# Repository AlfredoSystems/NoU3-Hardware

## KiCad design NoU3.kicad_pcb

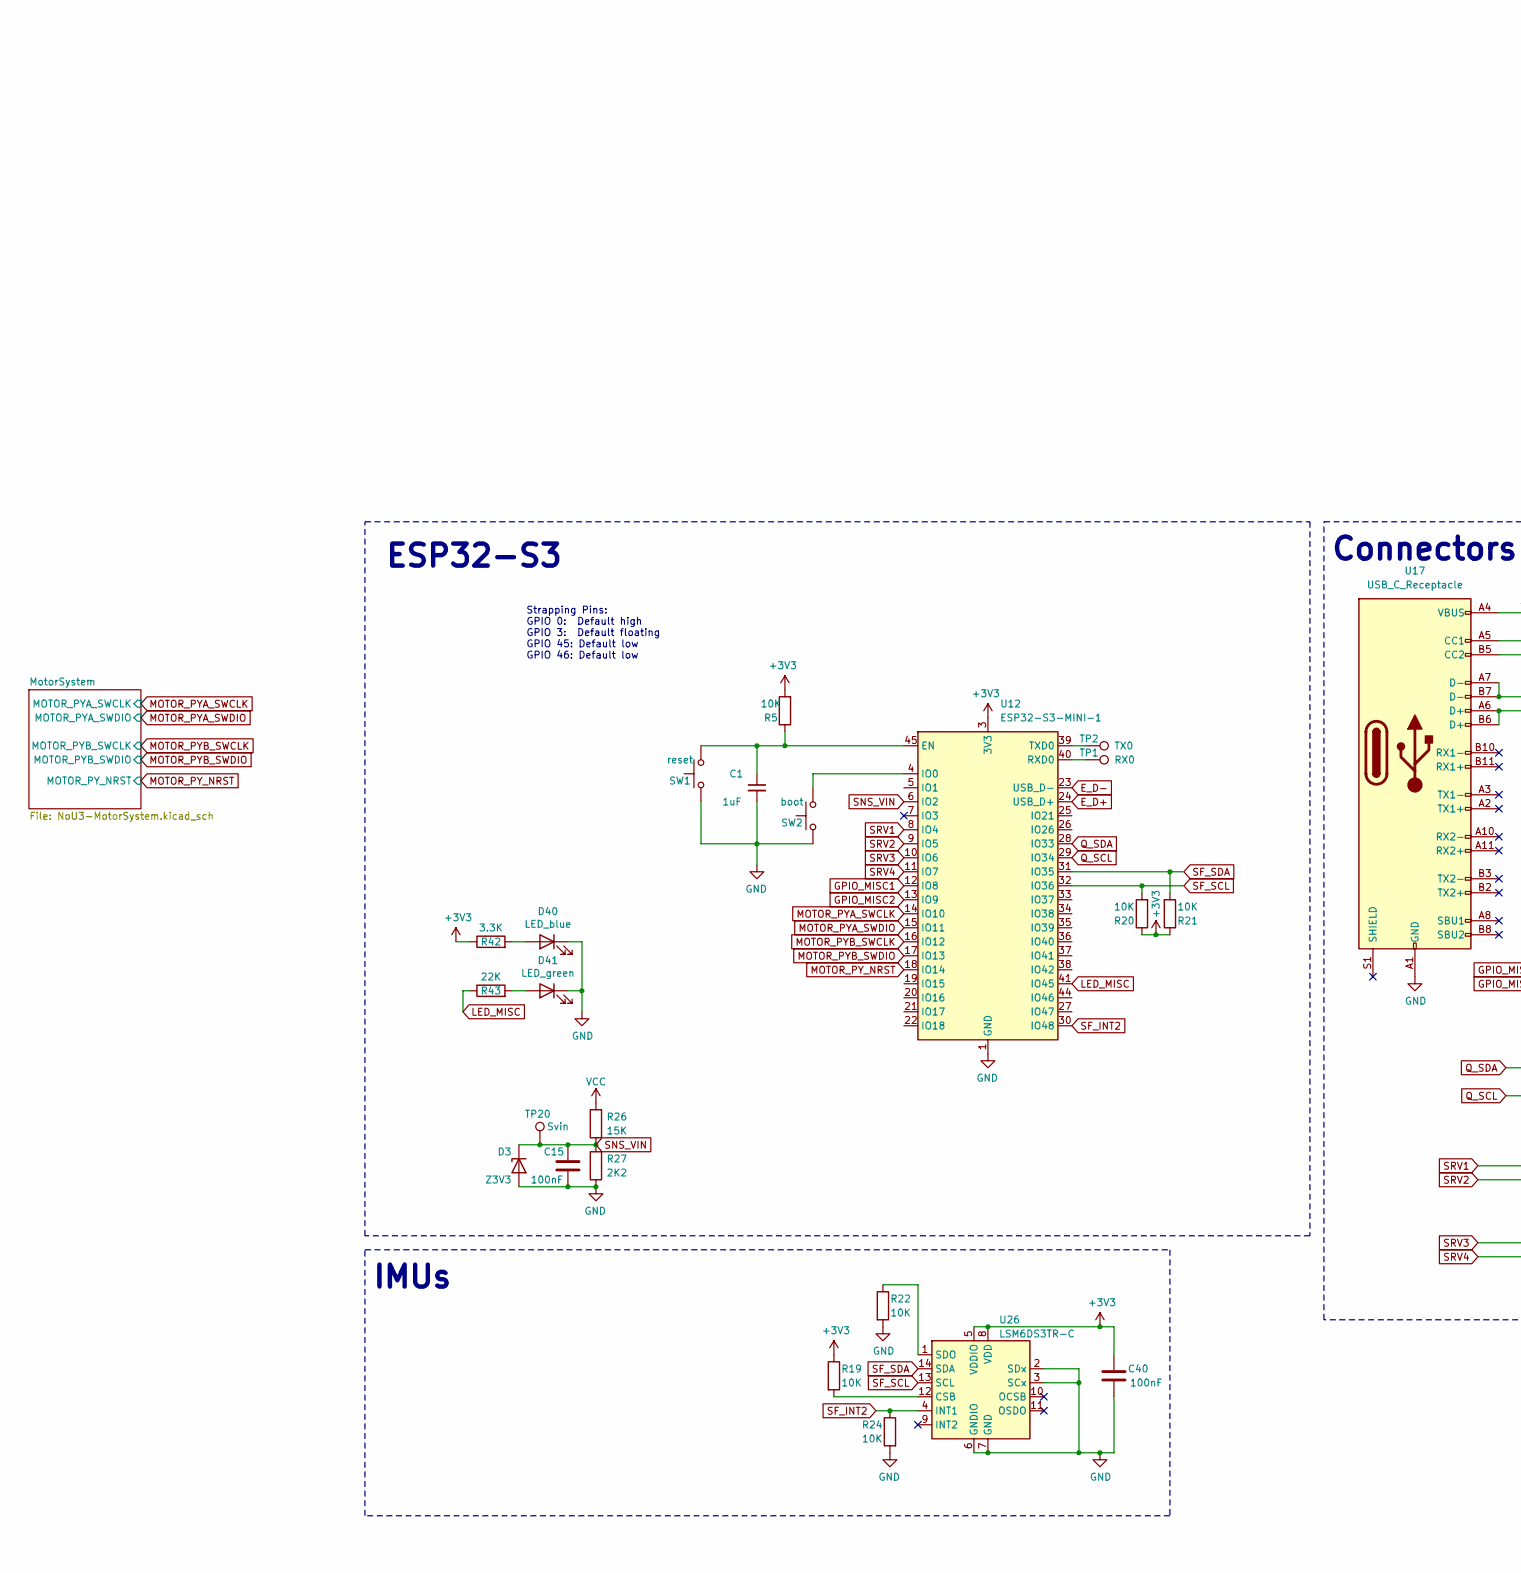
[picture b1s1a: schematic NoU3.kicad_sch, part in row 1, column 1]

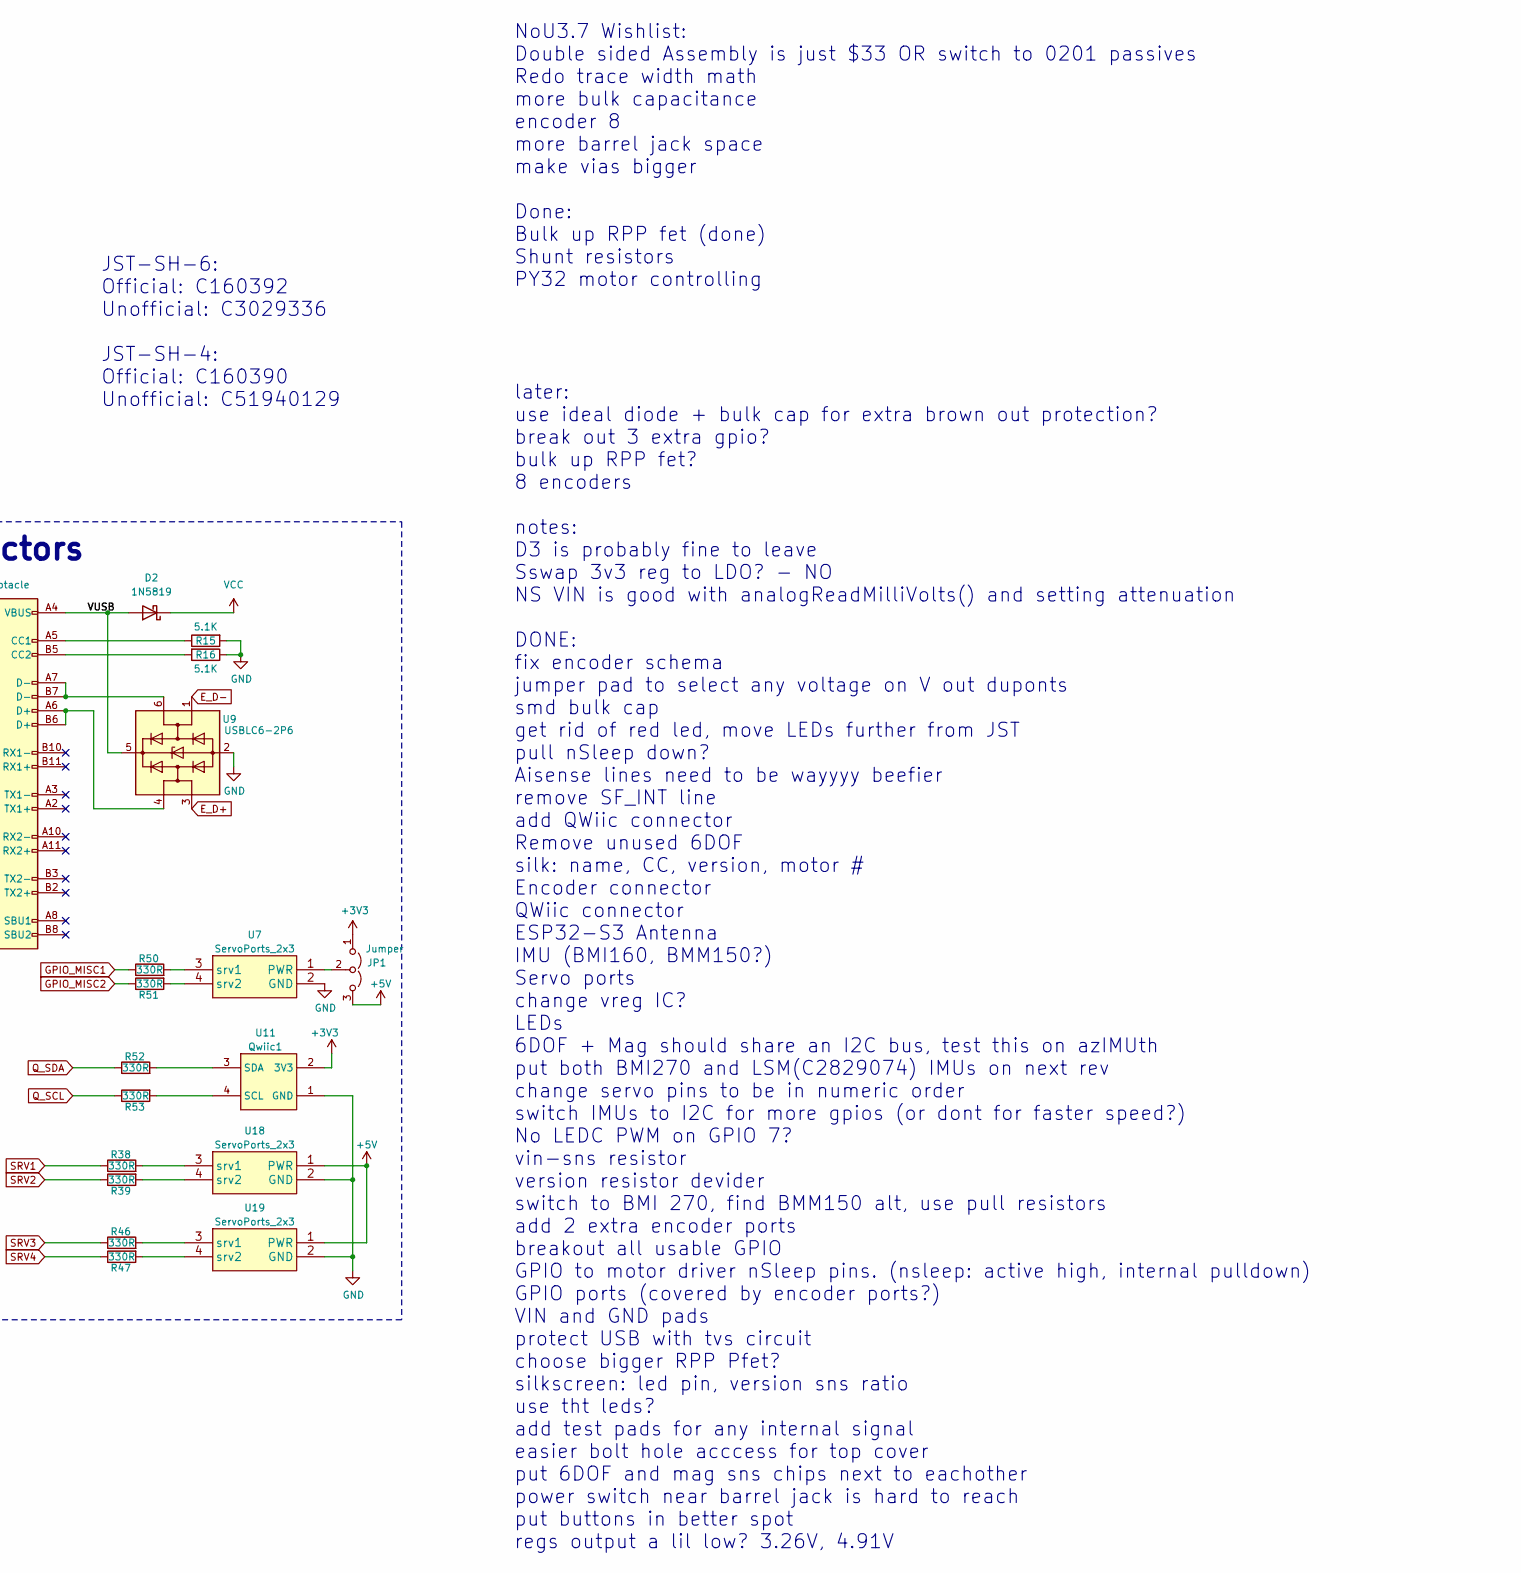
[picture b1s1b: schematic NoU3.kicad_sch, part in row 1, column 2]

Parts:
C1: 1uF; C_0402_1005Metric; LCSC C52923
C15, C40: 100nF; C_0402_1005Metric; LCSC C307331
D2: 1N5819; D_SOD-323; LCSC C191023
D3: Z3V3; D_SOD-323; LCSC C75073
D40: LED_blue; LED_0402_1005Metric; LCSC C130724
D41: LED_green; LED_0402_1005Metric; LCSC C965793
JP1: Jumper; SolderJumper-3-Small
R5, R19, R20, R21, R22, R24: 10K; R_0402_1005Metric; LCSC C25744
R15, R16: 5.1K; R_0402_1005Metric; LCSC C25905
R26: 15K; R_0402_1005Metric; LCSC C25756
R27: 2K2; R_0402_1005Metric; LCSC C25879
R38, R39, R46, R47, R50, R51, R52, R53: 330R; R_0402_1005Metric; LCSC C25104
R42: 3.3K; R_0402_1005Metric; LCSC C25890
R43: 22K; R_0402_1005Metric; LCSC C25768
SW1: reset; Button_SKRKAEE020; LCSC C115357
SW2: boot; Button_SKRKAEE020; LCSC C115357
TP1: RX0; PogoPad1
TP2: TX0; PogoPad1
TP20: Svin; PogoPad1
U7, U18, U19: ServoPorts_2x3; LCSC C5116479
U9: USBLC6-2P6; SOT-666; LCSC C2827693
U11: Qwiic1; JST_SH_BM04B-SRSS-TB_1x04-1MP_P1.00mm_Vertical; LCSC C51940129
U12: ESP32-S3-MINI-1; ESP32-S2-MINI-1; LCSC C2913206
U17: USB_C_Receptacle; USB_TYPE-C-31-M-12; LCSC C165948
U26: LSM6DS3TR-C; Bosch_LGA-14_3x2.5mm_P0.5mm; LCSC C967633

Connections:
+3V3: C40.1, JP1.1 (A), R5.2, R19.1, R20.1, R21.1, R42.1, U11.2 (3V3), U12.3 (3V3), U26.5 (VDDIO), U26.8 (VDD); also elsewhere on the board
+5V: JP1.3 (B), U18.1 (PWR), U19.1 (PWR); also elsewhere on the board
/VUSB: D2.2 (A), U9.5 (VBUS), U17.A4 (VBUS), U17.A9 (VBUS), U17.B4 (VBUS), U17.B9 (VBUS)
E_D+: U9.3 (I/O2), U12.24 (USB_D+)
E_D-: U9.1 (I/O1), U12.23 (USB_D-)
GND: C1.2, C15.2, C40.2, D3.2 (A), D40.1 (K), D41.1 (K), R15.2, R16.1, R22.2, R24.2, R27.1, SW1.2, SW2.2, U7.2 (GND), U9.2 (GND), U11.1 (GND), U12.1 (GND), U12.2 (GND), U12.42 (GND), U12.43 (GND), U12.46 (GND), U12.47 (GND), U12.48 (GND), U12.49 (GND), U12.50 (GND), U12.51 (GND), U12.52 (GND), U12.53 (GND), U12.54 (GND), U12.55 (GND), U12.56 (GND), U12.57 (GND), U12.58 (GND), U12.59 (GND), U12.60 (GND), U12.61 (GND), U12.62 (GND), U12.63 (GND), U12.64 (GND), U12.65 (GND), U17.A1 (GND), U17.A12 (GND), U17.B1 (GND), U17.B12 (GND), U18.2 (GND), U19.2 (GND), U26.2 (SDx), U26.3 (SCx), U26.6 (GNDIO), U26.7 (GND); also elsewhere on the board
GPIO_MISC1: R50.1, U12.12 (IO8)
GPIO_MISC2: R51.1, U12.13 (IO9)
LED_MISC: R43.1, U12.41 (IO45)
MOTOR_PYA_SWCLK: U12.14 (IO10); also elsewhere on the board
MOTOR_PYA_SWDIO: U12.15 (IO11); also elsewhere on the board
MOTOR_PYB_SWCLK: U12.16 (IO12); also elsewhere on the board
MOTOR_PYB_SWDIO: U12.17 (IO13); also elsewhere on the board
MOTOR_PY_NRST: U12.18 (IO14); also elsewhere on the board
unnamed: D40.2 (A), R42.2
unnamed: D41.2 (A), R43.2
unnamed: JP1.2 (C), U7.1 (PWR)
unnamed: R50.2, U7.3 (srv1)
unnamed: R51.2, U7.4 (srv2)
unnamed: R53.2, U11.4 (SCL)
unnamed: R52.2, U11.3 (SDA)
unnamed: C1.1, R5.1, SW1.1, U12.45 (EN)
unnamed: SW2.1, U12.4 (IO0)
unnamed: TP1.1 (1_1), U12.40 (RXD0)
unnamed: TP2.1 (1_1), U12.39 (TXD0)
unnamed: R15.1, U17.A5 (CC1)
unnamed: R16.2, U17.B5 (CC2)
unnamed: U9.4 (I/O2), U17.A6 (D+), U17.B6 (D+)
unnamed: U9.6 (I/O1), U17.A7 (D-), U17.B7 (D-)
unnamed: R38.2, U18.3 (srv1)
unnamed: R39.2, U18.4 (srv2)
unnamed: R46.2, U19.3 (srv1)
unnamed: R47.2, U19.4 (srv2)
unnamed: R19.2, U26.12 (CSB)
unnamed: R22.1, U26.1 (SDO)
Q_SCL: R53.1, U12.29 (IO34)
Q_SDA: R52.1, U12.28 (IO33)
SF_INT2: R24.1, U12.30 (IO48), U26.4 (INT1)
SF_SCL: R20.2, U12.32 (IO36), U26.13 (SCL)
SF_SDA: R21.2, U12.31 (IO35), U26.14 (SDA)
SNS_VIN: C15.1, D3.1 (K), R26.1, R27.2, TP20.1 (1_1), U12.6 (IO2)
SRV1: R38.1, U12.8 (IO4)
SRV2: R39.1, U12.9 (IO5)
SRV3: R46.1, U12.10 (IO6)
SRV4: R47.1, U12.11 (IO7)
VCC: D2.1 (K), R26.2; also elsewhere on the board

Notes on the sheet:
IMUs
Strapping Pins: GPIO 0: Default high GPIO 3: Default floating GPIO 45: Default low GPIO 46: Default low
NoU3.7 Wishlist: Double sided Assembly is just $33 OR switch to 0201 passives Redo trace width math more bulk capacitance encoder 8 more barrel jack space make vias bigger Done: Bulk up RPP fet (done) Shunt resistors PY32 motor controlling later: use ideal diode + bulk cap for extra brown out prote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
Connectors
ESP32-S3
JST-SH-6: Official: C160392 Unofficial: C3029336 JST-SH-4: Official: C160390 Unofficial: C51940129

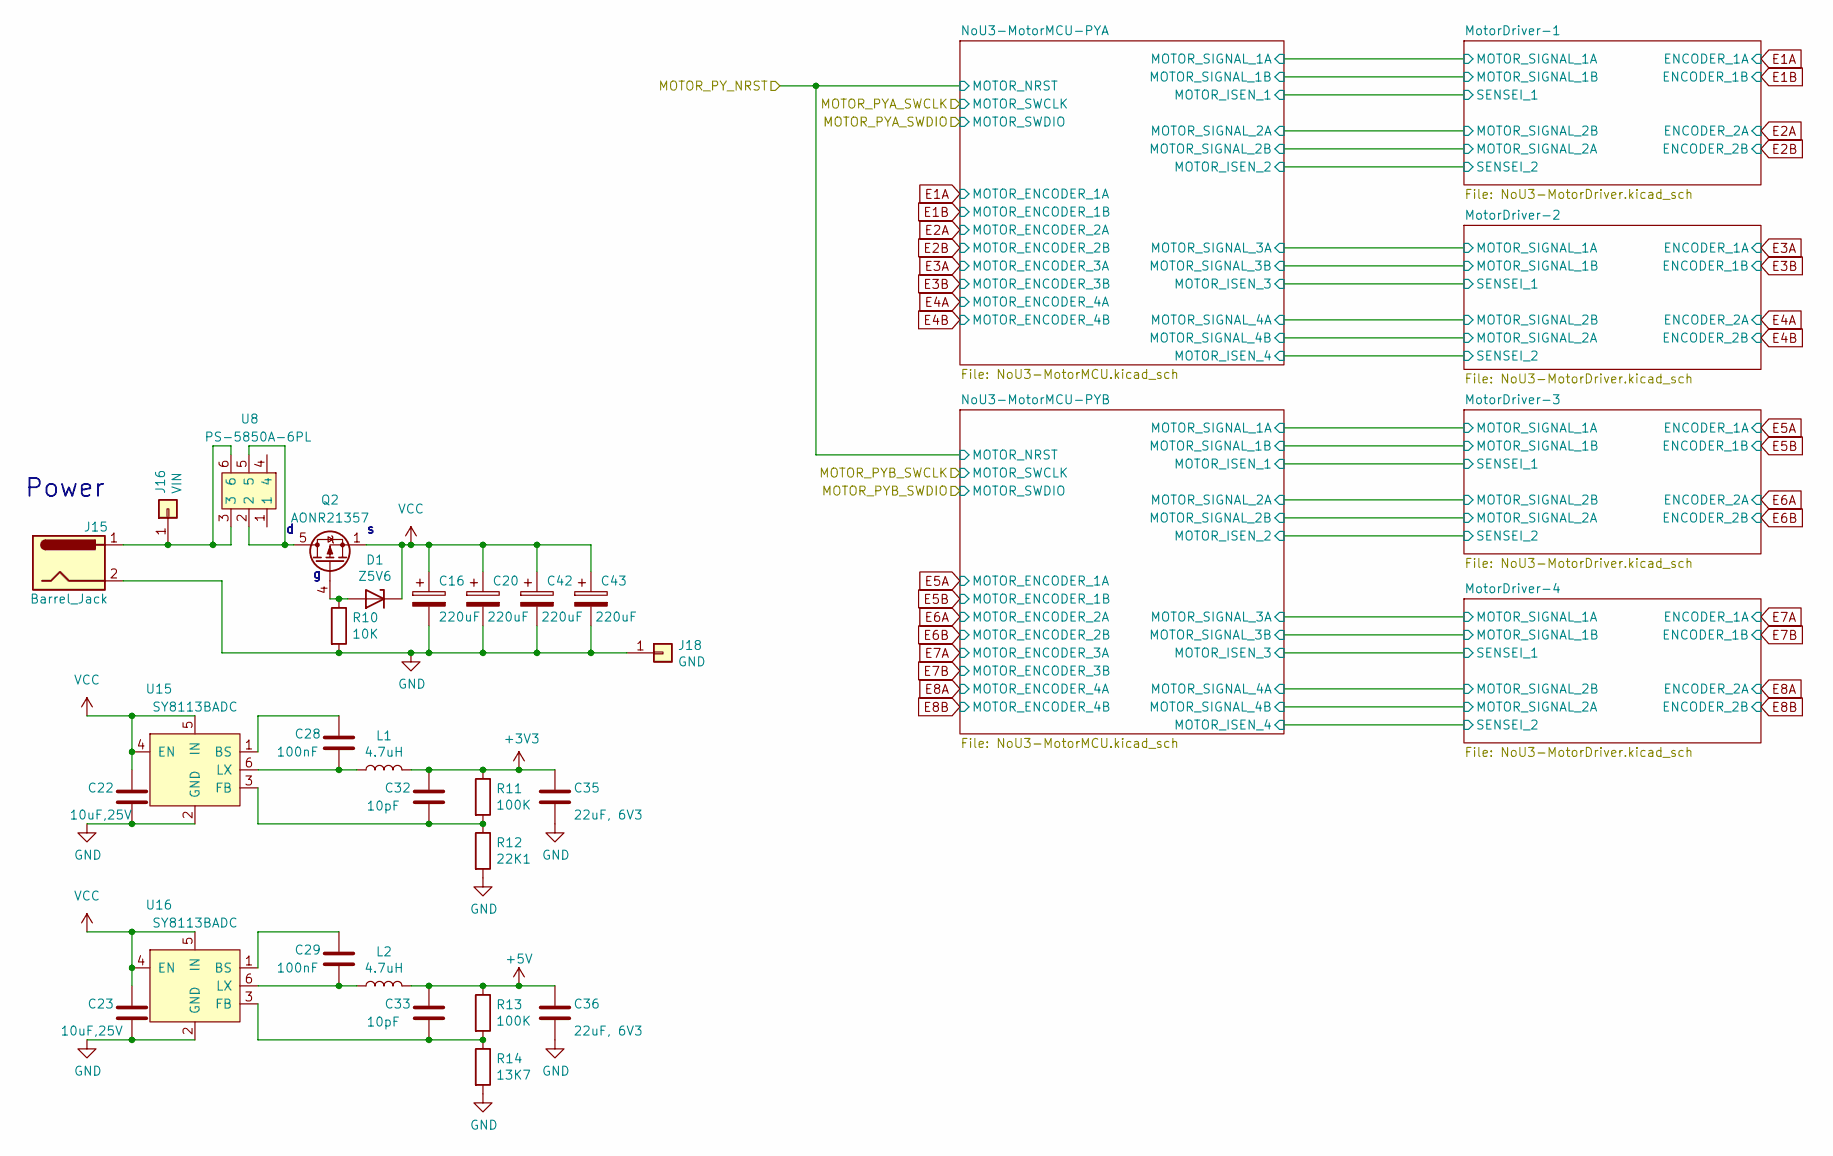
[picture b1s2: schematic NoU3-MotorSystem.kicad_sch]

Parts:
C16, C20, C42, C43: 220uF; CP_Elec_6.3x7.7_slim; LCSC C4747974
C22, C23: 10uF,25V; C_0603_1608Metric; LCSC C96446
C28, C29: 100nF; C_0402_1005Metric; LCSC C307331
C32, C33: 10pF; C_0402_1005Metric; LCSC C32949
C35, C36: 22uF, 6V3; C_0603_1608Metric; LCSC C59461
D1: Z5V6; D_SOD-323; LCSC C22612
J15: Barrel_Jack; DC-005C_1; LCSC C84007
J16: VIN; PinSocket_1x01_P2.54mm_Vertical
J18: GND; PinSocket_1x01_P2.54mm_Vertical
L1, L2: 4.7uH; LVF252A12; LCSC C88528
Q2: AONR21357; DFN-8-1EP_3x3mm_P0.65mm_EP1.55x2.4mm; LCSC C431196
R10: 10K; R_0402_1005Metric; LCSC C25744
R11, R13: 100K; R_0402_1005Metric; LCSC C25741
R12: 22K1; R_0402_1005Metric; LCSC C163478
R14: 13K7; R_0402_1005Metric; LCSC C25854
U8: PS-5850A-6PL; XKB5858-Z-75; LCSC C963201
U15, U16: SY8113BADC; TSOT-23-6; LCSC C78989

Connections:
+3V3: C32.1, C35.1, L1.2, R11.1; also elsewhere on the board
+5V: C33.1, C36.1, L2.2, R13.1; also elsewhere on the board
GND: C16.2, C20.2, C22.2, C23.2, C35.2, C36.2, C42.2, C43.2, J15.2, J18.1 (Pin_1_1), R10.2, R12.2, R14.2, U15.2 (GND), U16.2 (GND); also elsewhere on the board
unnamed: D1.2 (A), Q2.4 (G), R10.1
unnamed: J15.1, J16.1 (Pin_1_1), U8.3, U8.6
unnamed: Q2.5 (D), Q2.6 (D), Q2.7 (D), Q2.8 (D), Q2.9 (D), U8.2, U8.5
unnamed: C28.1, U15.1 (BS)
unnamed: C32.2, R11.2, R12.1, U15.3 (FB)
unnamed: C28.2, L1.1, U15.6 (LX)
unnamed: C29.1, U16.1 (BS)
unnamed: C33.2, R13.2, R14.1, U16.3 (FB)
unnamed: C29.2, L2.1, U16.6 (LX)
VCC: C16.1, C20.1, C22.1, C23.1, C42.1, C43.1, D1.1 (K), Q2.1 (S), Q2.2 (S), Q2.3 (S), U15.4 (EN), U15.5 (IN), U16.4 (EN), U16.5 (IN); also elsewhere on the board

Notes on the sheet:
Power

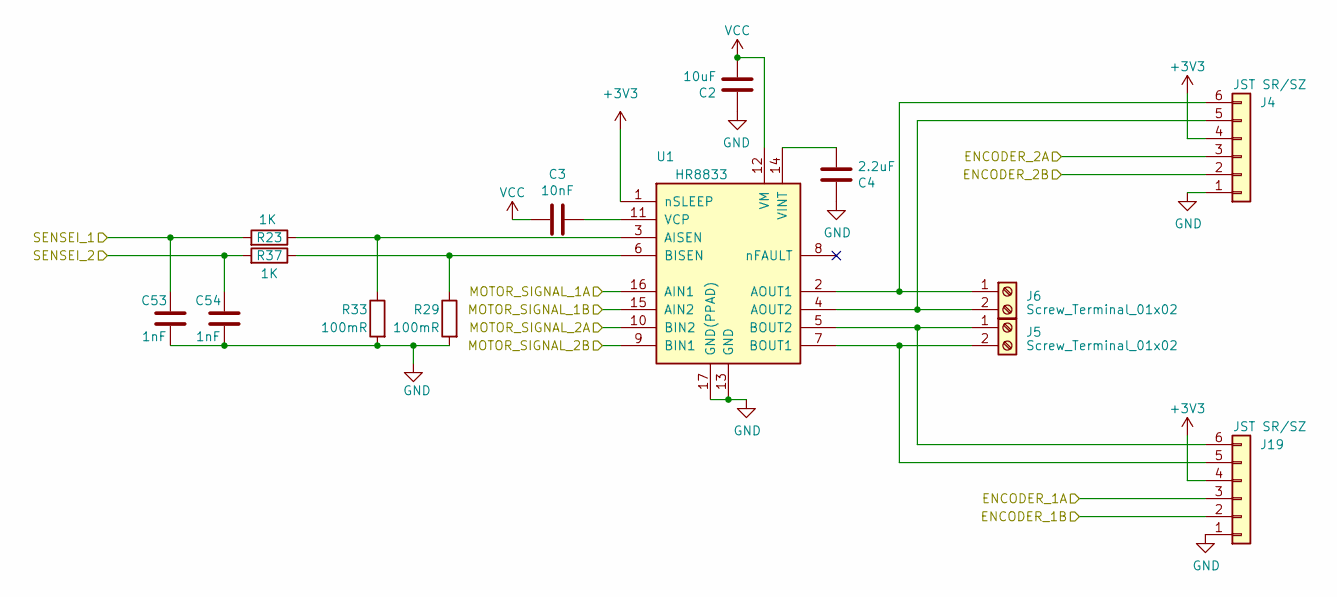
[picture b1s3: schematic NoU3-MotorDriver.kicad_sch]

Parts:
C2: 10uF; C_0805_2012Metric; LCSC C15850
C3: 10nF; C_0402_1005Metric; LCSC C15195
C4: 2.2uF; C_0402_1005Metric; LCSC C12530
C53, C54: 1nF; C_0402_1005Metric; LCSC C1523
J4, J19: JST SR/SZ; JST_SH_1x06_Vertical; LCSC C3029336
J5, J6: Screw_Terminal_01x02; TerminalBlock_Ningbo_2P_5mm; LCSC C557646
R23, R37: 1K; R_0402_1005Metric; LCSC C11702
R29, R33: 100mR; R_0805_2012Metric; LCSC C327057
U1: HR8833; HR8833-0.6mm; LCSC C128666

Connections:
+3V3: J4.4, J19.4, U1.1 (nSLEEP); also elsewhere on the board
/MotorSystem/MotorDriver-1/MOTOR_SIGNAL_1A: U1.16 (AIN1); also elsewhere on the board
/MotorSystem/MotorDriver-1/MOTOR_SIGNAL_1B: U1.15 (AIN2); also elsewhere on the board
/MotorSystem/MotorDriver-1/MOTOR_SIGNAL_2A: U1.10 (BIN2); also elsewhere on the board
/MotorSystem/MotorDriver-1/MOTOR_SIGNAL_2B: U1.9 (BIN1); also elsewhere on the board
/MotorSystem/MotorDriver-1/SENSEI_1: C53.1, R23.2; also elsewhere on the board
/MotorSystem/MotorDriver-1/SENSEI_2: C54.1, R37.2; also elsewhere on the board
E1A: J19.3; also elsewhere on the board
E1B: J19.2; also elsewhere on the board
E2A: J4.3; also elsewhere on the board
E2B: J4.2; also elsewhere on the board
GND: C2.2, C4.2, C53.2, C54.2, J4.1, J19.1, R29.2, R33.2, U1.13 (GND), U1.17 (GND(PPAD)); also elsewhere on the board
unnamed: J4.5, J6.2, U1.4 (AOUT2)
unnamed: J4.6, J6.1, U1.2 (AOUT1)
unnamed: J5.2, J19.5, U1.7 (BOUT1)
unnamed: J5.1, J19.6, U1.5 (BOUT2)
unnamed: R23.1, R33.1, U1.3 (AISEN)
unnamed: R29.1, R37.1, U1.6 (BISEN)
unnamed: C3.2, U1.11 (VCP)
unnamed: C4.1, U1.14 (VINT)
VCC: C2.1, C3.1, U1.12 (VM); also elsewhere on the board

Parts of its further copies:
C5, C8, C11: 10uF; C_0805_2012Metric; LCSC C15850
C6, C9, C12: 10nF; C_0402_1005Metric; LCSC C15195
C7, C10, C13: 2.2uF; C_0402_1005Metric; LCSC C12530
C49, C50, C55, C56, C59, C60: 1nF; C_0402_1005Metric; LCSC C1523
J1, J7, J10, J13, J17, J20: JST SR/SZ; JST_SH_1x06_Vertical; LCSC C3029336
J2, J3, J8, J9, J11, J12: Screw_Terminal_01x02; TerminalBlock_Ningbo_2P_5mm; LCSC C557646
R30, R31, R32, R34, R35, R36: 100mR; R_0805_2012Metric; LCSC C327057
R40, R41, R44, R45, R48, R49: 1K; R_0402_1005Metric; LCSC C11702
U4, U5, U6: HR8833; HR8833-0.6mm; LCSC C128666

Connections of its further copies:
+3V3: J1.4, J7.4, J10.4, J13.4, J17.4, J20.4, U4.1 (nSLEEP), U5.1 (nSLEEP), U6.1 (nSLEEP); also elsewhere on the board
/MotorSystem/MotorDriver-2/MOTOR_SIGNAL_1A: U4.16 (AIN1); also elsewhere on the board
/MotorSystem/MotorDriver-2/MOTOR_SIGNAL_1B: U4.15 (AIN2); also elsewhere on the board
/MotorSystem/MotorDriver-2/MOTOR_SIGNAL_2A: U4.10 (BIN2); also elsewhere on the board
/MotorSystem/MotorDriver-2/MOTOR_SIGNAL_2B: U4.9 (BIN1); also elsewhere on the board
/MotorSystem/MotorDriver-2/SENSEI_1: C55.1, R40.2; also elsewhere on the board
/MotorSystem/MotorDriver-2/SENSEI_2: C56.1, R41.2; also elsewhere on the board
/MotorSystem/MotorDriver-3/MOTOR_SIGNAL_1A: U5.16 (AIN1); also elsewhere on the board
/MotorSystem/MotorDriver-3/MOTOR_SIGNAL_1B: U5.15 (AIN2); also elsewhere on the board
/MotorSystem/MotorDriver-3/MOTOR_SIGNAL_2A: U5.10 (BIN2); also elsewhere on the board
/MotorSystem/MotorDriver-3/MOTOR_SIGNAL_2B: U5.9 (BIN1); also elsewhere on the board
/MotorSystem/MotorDriver-3/SENSEI_1: C49.1, R44.2; also elsewhere on the board
/MotorSystem/MotorDriver-3/SENSEI_2: C50.1, R45.2; also elsewhere on the board
/MotorSystem/MotorDriver-4/MOTOR_SIGNAL_1A: U6.16 (AIN1); also elsewhere on the board
/MotorSystem/MotorDriver-4/MOTOR_SIGNAL_1B: U6.15 (AIN2); also elsewhere on the board
/MotorSystem/MotorDriver-4/MOTOR_SIGNAL_2A: U6.10 (BIN2); also elsewhere on the board
/MotorSystem/MotorDriver-4/MOTOR_SIGNAL_2B: U6.9 (BIN1); also elsewhere on the board
/MotorSystem/MotorDriver-4/SENSEI_1: C59.1, R48.2; also elsewhere on the board
/MotorSystem/MotorDriver-4/SENSEI_2: C60.1, R49.2; also elsewhere on the board
E3A: J7.3; also elsewhere on the board
E3B: J7.2; also elsewhere on the board
E4A: J13.3; also elsewhere on the board
E4B: J13.2; also elsewhere on the board
E5A: J10.3; also elsewhere on the board
E5B: J10.2; also elsewhere on the board
E6A: J17.3; also elsewhere on the board
E6B: J17.2; also elsewhere on the board
E7A: J1.3; also elsewhere on the board
E7B: J1.2; also elsewhere on the board
E8A: J20.3; also elsewhere on the board
E8B: J20.2; also elsewhere on the board
GND: C5.2, C7.2, C8.2, C10.2, C11.2, C13.2, C49.2, C50.2, C55.2, C56.2, C59.2, C60.2, J1.1, J7.1, J10.1, J13.1, J17.1, J20.1, R30.2, R31.2, R32.2, R34.2, R35.2, R36.2, U4.13 (GND), U4.17 (GND(PPAD)), U5.13 (GND), U5.17 (GND(PPAD)), U6.13 (GND), U6.17 (GND(PPAD)); also elsewhere on the board
unnamed: J1.5, J2.2, U6.7 (BOUT1)
unnamed: J1.6, J2.1, U6.5 (BOUT2)
unnamed: J7.5, J8.2, U4.7 (BOUT1)
unnamed: J7.6, J8.1, U4.5 (BOUT2)
unnamed: J10.5, J11.2, U5.7 (BOUT1)
unnamed: J10.6, J11.1, U5.5 (BOUT2)
unnamed: J12.1, J17.6, U5.2 (AOUT1)
unnamed: J12.2, J17.5, U5.4 (AOUT2)
unnamed: J9.2, J13.5, U4.4 (AOUT2)
unnamed: J9.1, J13.6, U4.2 (AOUT1)
unnamed: J3.2, J20.5, U6.4 (AOUT2)
unnamed: J3.1, J20.6, U6.2 (AOUT1)
unnamed: R34.1, R40.1, U4.3 (AISEN)
unnamed: R30.1, R41.1, U4.6 (BISEN)
unnamed: C6.2, U4.11 (VCP)
unnamed: C7.1, U4.14 (VINT)
unnamed: R35.1, R44.1, U5.3 (AISEN)
unnamed: R31.1, R45.1, U5.6 (BISEN)
unnamed: C9.2, U5.11 (VCP)
unnamed: C10.1, U5.14 (VINT)
unnamed: R36.1, R48.1, U6.3 (AISEN)
unnamed: R32.1, R49.1, U6.6 (BISEN)
unnamed: C12.2, U6.11 (VCP)
unnamed: C13.1, U6.14 (VINT)
VCC: C5.1, C6.1, C8.1, C9.1, C11.1, C12.1, U4.12 (VM), U5.12 (VM), U6.12 (VM); also elsewhere on the board

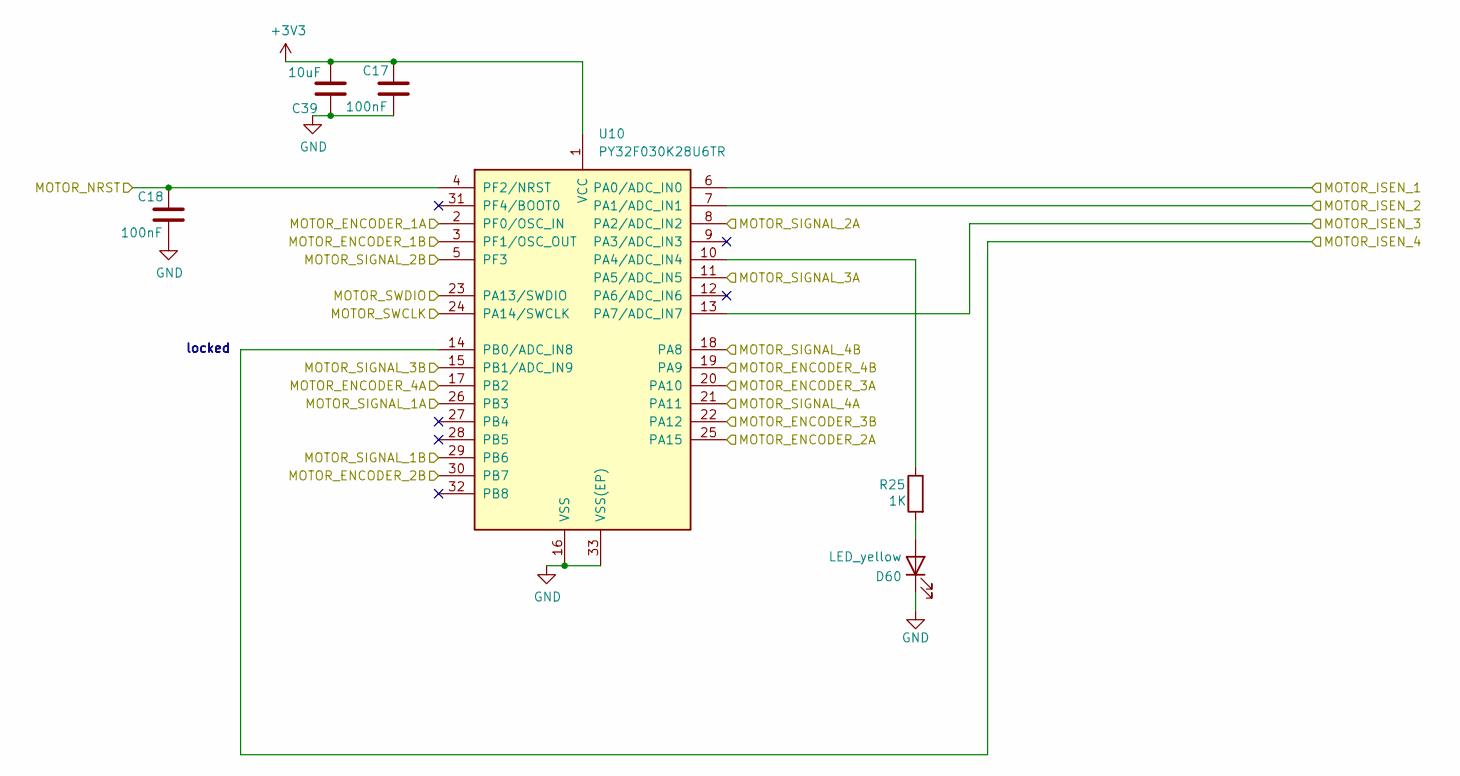
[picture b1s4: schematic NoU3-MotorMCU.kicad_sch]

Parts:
C17, C18: 100nF; C_0402_1005Metric; LCSC C307331
C39: 10uF; C_0402_1005Metric; LCSC C15525
D60: LED_yellow; LED_0402_1005Metric; LCSC C130721
R25: 1K; R_0402_1005Metric; LCSC C11702
U10: PY32F030K28U6TR; VQFN-32-1EP_5x5mm_P0.5mm_EP3.5x3.5mm; LCSC C3018718

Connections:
+3V3: C17.1, C39.2, U10.1 (VCC); also elsewhere on the board
/MotorSystem/MotorDriver-1/MOTOR_SIGNAL_1A: U10.26 (PB3); also elsewhere on the board
/MotorSystem/MotorDriver-1/MOTOR_SIGNAL_1B: U10.29 (PB6); also elsewhere on the board
/MotorSystem/MotorDriver-1/MOTOR_SIGNAL_2A: U10.5 (PF3); also elsewhere on the board
/MotorSystem/MotorDriver-1/MOTOR_SIGNAL_2B: U10.8 (PA2/ADC_IN2); also elsewhere on the board
/MotorSystem/MotorDriver-1/SENSEI_1: U10.6 (PA0/ADC_IN0); also elsewhere on the board
/MotorSystem/MotorDriver-1/SENSEI_2: U10.7 (PA1/ADC_IN1); also elsewhere on the board
/MotorSystem/MotorDriver-2/MOTOR_SIGNAL_1A: U10.11 (PA5/ADC_IN5); also elsewhere on the board
/MotorSystem/MotorDriver-2/MOTOR_SIGNAL_1B: U10.15 (PB1/ADC_IN9); also elsewhere on the board
/MotorSystem/MotorDriver-2/MOTOR_SIGNAL_2A: U10.18 (PA8); also elsewhere on the board
/MotorSystem/MotorDriver-2/MOTOR_SIGNAL_2B: U10.21 (PA11); also elsewhere on the board
/MotorSystem/MotorDriver-2/SENSEI_1: U10.13 (PA7/ADC_IN7); also elsewhere on the board
/MotorSystem/MotorDriver-2/SENSEI_2: U10.14 (PB0/ADC_IN8); also elsewhere on the board
E1A: U10.2 (PF0/OSC_IN); also elsewhere on the board
E1B: U10.3 (PF1/OSC_OUT); also elsewhere on the board
E2A: U10.25 (PA15); also elsewhere on the board
E2B: U10.30 (PB7); also elsewhere on the board
E3A: U10.20 (PA10); also elsewhere on the board
E3B: U10.22 (PA12); also elsewhere on the board
E4A: U10.17 (PB2); also elsewhere on the board
E4B: U10.19 (PA9); also elsewhere on the board
GND: C17.2, C18.2, C39.1, D60.1 (K), U10.16 (VSS), U10.33 (VSS(EP)); also elsewhere on the board
MOTOR_PYA_SWCLK: U10.24 (PA14/SWCLK); also elsewhere on the board
MOTOR_PYA_SWDIO: U10.23 (PA13/SWDIO); also elsewhere on the board
MOTOR_PY_NRST: C18.1, U10.4 (PF2/NRST); also elsewhere on the board
unnamed: D60.2 (A), R25.2
unnamed: R25.1, U10.10 (PA4/ADC_IN4)

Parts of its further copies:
C46, C48: 100nF; C_0402_1005Metric; LCSC C307331
C47: 10uF; C_0402_1005Metric; LCSC C15525
D61: LED_yellow; LED_0402_1005Metric; LCSC C130721
R28: 1K; R_0402_1005Metric; LCSC C11702
U14: PY32F030K28U6TR; VQFN-32-1EP_5x5mm_P0.5mm_EP3.5x3.5mm; LCSC C3018718

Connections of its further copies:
+3V3: C47.2, C48.1, U14.1 (VCC); also elsewhere on the board
/MotorSystem/MotorDriver-3/MOTOR_SIGNAL_1A: U14.26 (PB3); also elsewhere on the board
/MotorSystem/MotorDriver-3/MOTOR_SIGNAL_1B: U14.29 (PB6); also elsewhere on the board
/MotorSystem/MotorDriver-3/MOTOR_SIGNAL_2A: U14.5 (PF3); also elsewhere on the board
/MotorSystem/MotorDriver-3/MOTOR_SIGNAL_2B: U14.8 (PA2/ADC_IN2); also elsewhere on the board
/MotorSystem/MotorDriver-3/SENSEI_1: U14.6 (PA0/ADC_IN0); also elsewhere on the board
/MotorSystem/MotorDriver-3/SENSEI_2: U14.7 (PA1/ADC_IN1); also elsewhere on the board
/MotorSystem/MotorDriver-4/MOTOR_SIGNAL_1A: U14.11 (PA5/ADC_IN5); also elsewhere on the board
/MotorSystem/MotorDriver-4/MOTOR_SIGNAL_1B: U14.15 (PB1/ADC_IN9); also elsewhere on the board
/MotorSystem/MotorDriver-4/MOTOR_SIGNAL_2A: U14.18 (PA8); also elsewhere on the board
/MotorSystem/MotorDriver-4/MOTOR_SIGNAL_2B: U14.21 (PA11); also elsewhere on the board
/MotorSystem/MotorDriver-4/SENSEI_1: U14.13 (PA7/ADC_IN7); also elsewhere on the board
/MotorSystem/MotorDriver-4/SENSEI_2: U14.14 (PB0/ADC_IN8); also elsewhere on the board
E5A: U14.2 (PF0/OSC_IN); also elsewhere on the board
E5B: U14.3 (PF1/OSC_OUT); also elsewhere on the board
E6A: U14.25 (PA15); also elsewhere on the board
E6B: U14.30 (PB7); also elsewhere on the board
E7A: U14.20 (PA10); also elsewhere on the board
E7B: U14.22 (PA12); also elsewhere on the board
E8A: U14.17 (PB2); also elsewhere on the board
E8B: U14.19 (PA9); also elsewhere on the board
GND: C46.2, C47.1, C48.2, D61.1 (K), U14.16 (VSS), U14.33 (VSS(EP)); also elsewhere on the board
MOTOR_PYB_SWCLK: U14.24 (PA14/SWCLK); also elsewhere on the board
MOTOR_PYB_SWDIO: U14.23 (PA13/SWDIO); also elsewhere on the board
MOTOR_PY_NRST: C46.1, U14.4 (PF2/NRST); also elsewhere on the board
unnamed: D61.2 (A), R28.2
unnamed: R28.1, U14.10 (PA4/ADC_IN4)

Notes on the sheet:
locked

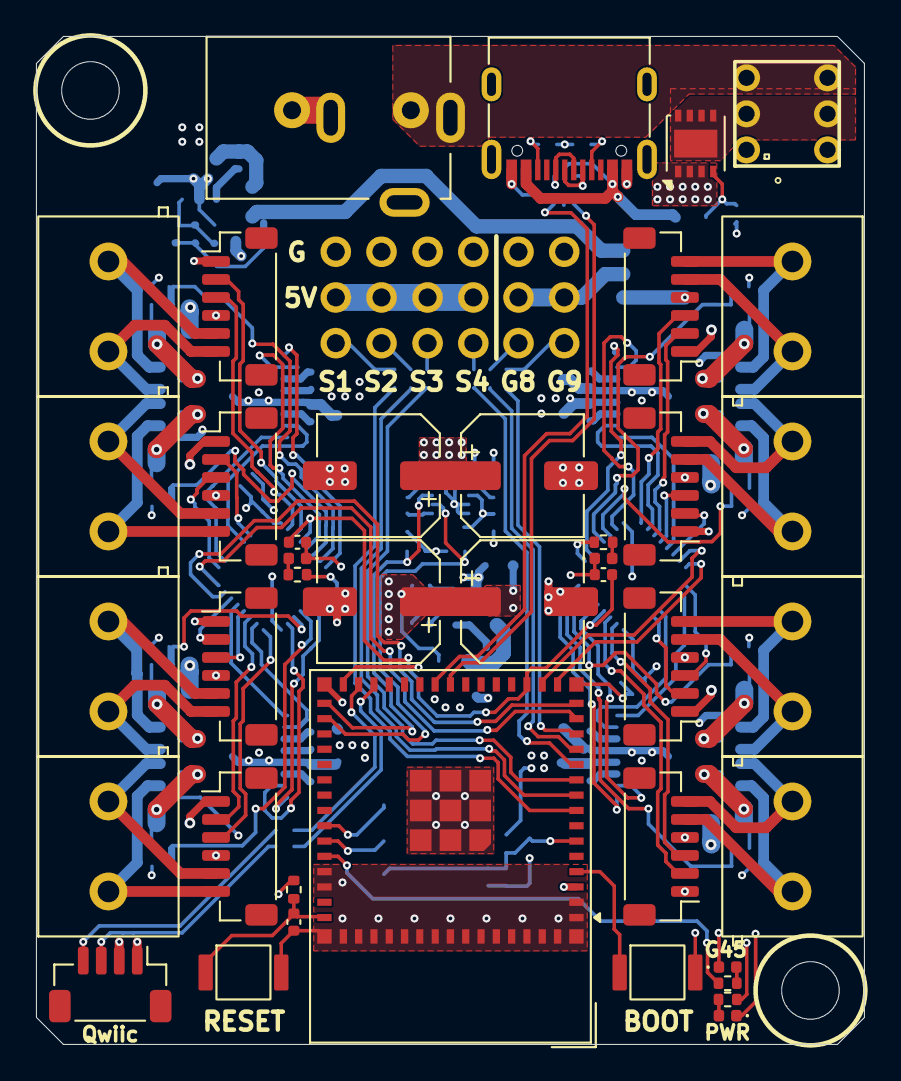
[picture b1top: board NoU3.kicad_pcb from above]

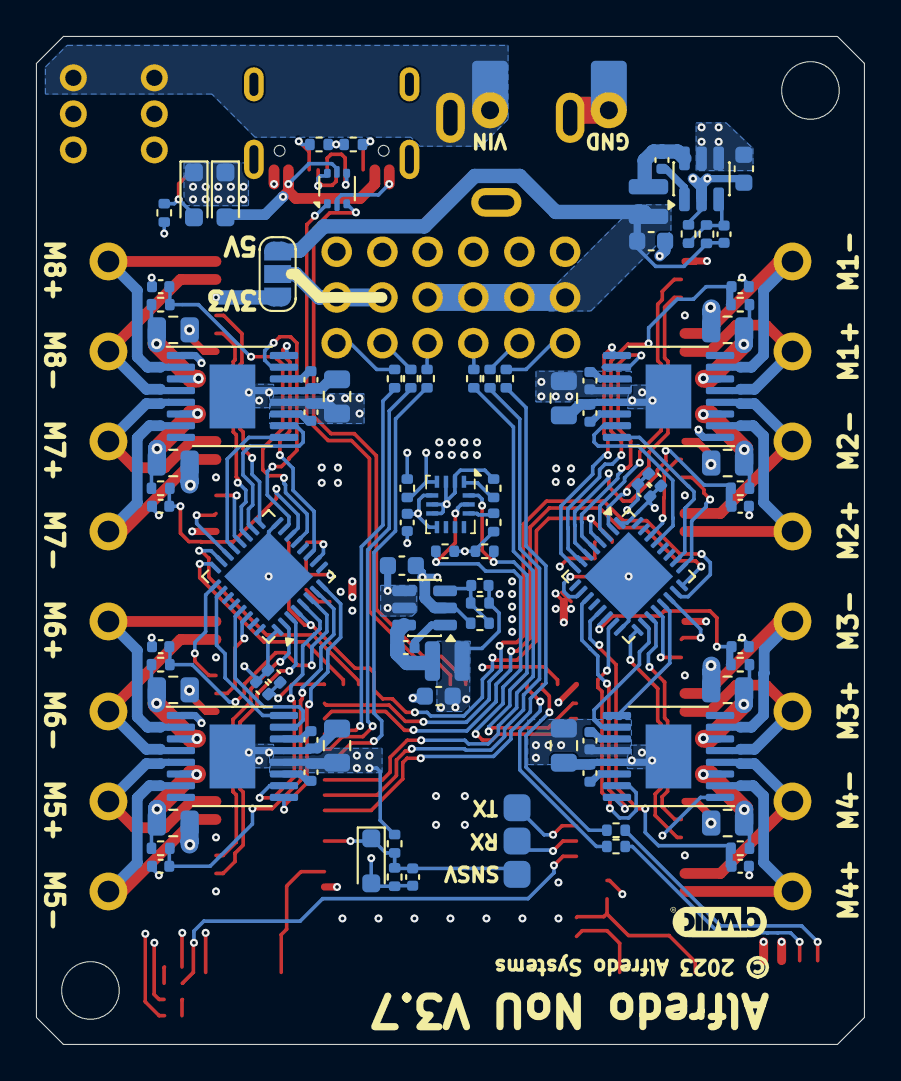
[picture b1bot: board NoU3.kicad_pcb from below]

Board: 4 copper layers, 46.0 x 56.0 mm, 142 parts (93 on the bottom side), 131 nets.

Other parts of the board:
H1, H2: (no value)
TAB1, TAB2, TAB3, TAB4: Tab

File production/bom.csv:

Designator,Footprint,Quantity,Value,LCSC Part #
C1,0402,1,1uF,C52923
"C10, C13, C4, C7",0402,4,2.2uF,C12530
"C11, C2, C5, C8",0805,4,10uF,C15850
"C12, C3, C6, C9",0402,4,10nF,C15195
"C15, C17, C18, C28, C29, C40, C46, C48",0402,8,100nF,C307331
"C16, C20, C42, C43",CP_Elec_6.3x7.7_slim,4,220uF,C4747974
"C22, C23",0603,2,"10uF,25V",C96446
"C32, C33",0402,2,10pF,C32949
"C35, C36",0603,2,"22uF, 6V3",C59461
"C39, C47",0402,2,10uF,C15525
"C49, C50, C53, C54, C55, C56, C59, C60",0402,8,1nF,C1523 
D1,D_SOD-323,1,Z5V6,C22612
D2,D_SOD-323,1,1N5819,C191023
D3,D_SOD-323,1,Z3V3,C75073
D40,0402,1,LED_blue,C130724
D41,0402,1,LED_green,C965793
"D60, D61",0402,2,LED_yellow,C130721
"J1, J10, J13, J17, J19, J20, J4, J7",JST_SH_1x06_Vertical,8,JST SR/SZ,C3029336 
"J11, J12, J2, J3, J5, J6, J8, J9",TerminalBlock_Ningbo_2P_5mm,8,Screw_Terminal_01x02,C557646
J15,DC-005C_1,1,Barrel_Jack,C84007
J16,PinSocket_1x01_P2.54mm_Vertical,1,VIN,
J18,PinSocket_1x01_P2.54mm_Vertical,1,GND,
"L1, L2",LVF252A12,2,4.7uH,C88528
Q2,DFN-8-1EP_3x3mm_P0.65mm_EP1.55x2.4mm,1,AONR21357,C431196
"R10, R19, R20, R21, R22, R24, R5",0402,7,10K,C25744
"R11, R13",0402,2,100K,C25741
R12,0402,1,22K1,C163478 
R14,0402,1,13K7,C25854
"R15, R16",0402,2,5.1K,C25905
"R23, R25, R28, R37, R40, R41, R44, R45, R48, R49",0402,10,1K,C11702
R26,0402,1,15K,C25756
R27,0402,1,2K2,C25879
"R29, R30, R31, R32, R33, R34, R35, R36",0805,8,100mR,C327057
"R38, R39, R46, R47, R50, R51, R52, R53",0402,8,330R,C25104
R42,0402,1,3.3K,C25890
R43,0402,1,22K,C25768
SW1,Button_SKRKAEE020,1,reset,C115357
SW2,Button_SKRKAEE020,1,boot,C115357
TP1,PogoPad1,1,RX0,
TP2,PogoPad1,1,TX0,
TP20,PogoPad1,1,Svin,
"U1, U4, U5, U6",HR8833-0.6mm,4,HR8833,C128666
"U10, U14",VQFN-32-1EP_5x5mm_P0.5mm_EP3.5x3.5mm,2,PY32F030K28U6TR,C3018718
U11,JST_SH_BM04B-SRSS-TB_1x04-1MP_P1.00mm_Vertical,1,Qwiic1,C51940129
U12,ESP32-S2-MINI-1,1,ESP32-S3-MINI-1,C2913206 
"U15, U16",TSOT-23-6,2,SY8113BADC,C78989
U17,USB_TYPE-C-31-M-12,1,USB_C_Receptacle,C165948
"U18, U19, U7",ServoPorts_2x3,3,ServoPorts_2x3,C5116479
U26,Bosch_LGA-14_3x2.5mm_P0.5mm,1,LSM6DS3TR-C,C967633
U8,XKB5858-Z-75,1,PS-5850A-6PL,C963201
U9,SOT-666,1,USBLC6-2P6,C2827693

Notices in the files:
NoU3.kicad_pcb:
© 2023 Alfredo Systems
